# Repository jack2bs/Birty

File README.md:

# Birty the Robot

Birty is a recursive backronym for Birty Is a Robot, Thank You.

As part of my getting acquainted with robotics so as to continue in a leadership capacity in the Princeton Robotics Club, I set out to build a classic and simple, but well designed and well programmed robot which could drive in straight lines, turn accurate angles, avoid obstacles in it's path, and do it all autonomously. While these goals may not sound particularly ambitious or impressive, they are the baseline and the scaffolding for what a robot needs to be able to do.

I am proud of Birty. Birty is my most polished large project to date. The part-selection was, with one exception, well thought out. The electronics are well designed. The 3d structure of the Robot was well planned. The code is well written; it's fast, self-documenting (and documented with comments), and highly functional.

My success building Birty came on the back of the shortcomings of past projects, some of which never lived up to their potential simply due to my mistakes and inexperience. I learned from my mistakes, and I improved. I organized the project better. I worked with each sensor and electrical component before I used them to make sure they functioned as I expected them to. I tested each bit of code before moving onto another function. I took the time to do things right, and in the end it was the fastest I've ever completed a project. 

# Parts and justifications

+ Microcontroller
	+ 1 x [ATMEGA32u4](https://www.digikey.com/en/products/detail/microchip-technology/ATMEGA32U4-AUR/2238241)
	+ The Atmega32u4 is more than powerful enough for the tasks laid out, and since I had experience with it and had some in my supplies (every MCU was out of stock at the time), this was a no-brainer. An I2C bus (using the TWI peripheral) for sensor communications, USART for debugging over bluetooth, GPIO for driving motors, pin change interrupts for reading encoders, and more than enough timers for task scheduling.
+ Distance Sensors
	+ 8 x [Adafruit VL6180x](https://www.adafruit.com/product/3316)
	+ The VL6180x from STM was a good choice because it has great accuracy at low distance ranges which is extremely important for obstacle detection and avoidance for a robot of Birty's size. I chose the 6180x over other sensors in the lineup since it is the only one with a register map available, allowing me to bypass STM's poorly regarded API and simply build an I2C communication layer myself. I chose the Adafruit breakouts so that I wouldn't have to make them myself, and so that I had logic level shifting from 5v to 3.3v on both the interrupt and xshut signal lines.
+ Gyroscope
	+ 1 x [MinImu-9 v5](https://www.pololu.com/product/2738)
	+ This was perhaps the one mistake I made in part selection. The MiniImu-9 v5 from Polulu is a good IMU, but it doesn't have onboard fusion calculation and the speed of the Atmega32u4 makes a complex fusion calculation a challenge. In the future I would lean more towards something like a BNO055 from Bosch, which has on board fusion calculations and outputs roll pitch and yaw, as opposed to x, y, and z for a gyroscope, accelerometer, and magnetometer seperately.
+ Motors
	+ 2 x [Regular DC motors](https://www.adafruit.com/product/4639)
	+ 2 x [Stepper Motors](https://www.adafruit.com/product/4411)
	+ I have both stepper and DC motors and I am able to interchange them as I see fit. The choices here weren't too important but I wanted them as small as I could find, and so that is what I got. 
+ Motor mounts
	+ 1 x [DC Motor Mount](https://www.pololu.com/product/989)
	+ 2 x [Stepper Mount](https://www.pololu.com/product/3435)
+ DC Motor Driver (H Bridge)
	+ 4 x [H Bridges](https://www.adafruit.com/product/4489)
	+ I tested these H bridges on a breadboard before using them on Birty and they proved to be simple and effective.
+ Wheels
	+ 1 x (2 wheels) [Wheel pair](https://www.pololu.com/product/1424)
	+ I wanted somewhat large wheels to attempt to improve Birty's ability to handle semi-rough terrain (carpet).
+ Universal Mounting Hubs
	+ 1 x (2 hubs) [Mounting hub pair](https://www.pololu.com/product/1997)
+ Ball Casters
	+ 2 x [Ball casters](https://www.pololu.com/product/955)
	+ These were so that Birty wouldn't tilt forwards or backwards.
+ Spacers
	+ 1 x [2mm spacers](https://www.pololu.com/product/1980)
	+ 1 x [4mm spacers](https://www.pololu.com/product/1981)
	+ To space the ball casters to the right height.
+ Battery
	+ 1 x [CHAMP Portable Charger](https://www.gonimble.com/products/champ-portable-charger)
	+ I chose this battery pack because it was the smallest I could find and because I am a sucker for sustainability.
+ Battery Mounting
	+ 3 x [Battery Mounts](https://www.pololu.com/product/2677)
	+ I'll explain the battery mounting strategy further when I get to mechanical design.
+ Wire to Board conns
	+ 2 x [6 Pos Wire to Board](https://www.digikey.com/en/products/detail/on-shore-technology-inc/OSTVN06A150/1588866) and 1 x [2 Pos Wire to Board](https://www.digikey.com/en/products/detail/on-shore-technology-inc/OSTVN02A150/1588862)
+ Shift registers
	+  1 x [Shift Register](https://www.digikey.com/en/products/detail/texas-instruments/SN74HCS264DR/13562988)
	+ I'll get into the purpose of the shift register when I discuss the electronics.
+ Assorted SMD Resistors and Capacitors
	+ 3 x 5k R
	+ 2 x 10k R
	+ 1 x 100 R
	+ 2 x 22 R
	+ 6 x 0.1uF C
	+ 1 x 1uF C
	+ 2 x 22pF C
	+ Pushbuttons
	+ 16Mhz Crystal
	+ USB Receptacle
+ Header Pins
	+ 9 x [6 Pos Female Header pins](https://www.digikey.com/en/products/detail/sullins-connector-solutions/PPPC061LFBN-RC/810178)
	+ 1 x [5 Pos Female Header Pins](https://www.digikey.com/en/products/detail/sullins-connector-solutions/PPPC051LFBN-RC/810177)

# Electrical design
After choosing parts I set out to design the schematic and circuit boards. This process was relatively straight forward, except I had to find a way to use as few GPIO pins as possible. The first measure I took was introducing a shift register to access the xshut pins on the 8 VL6180x sensors. I needed to be able to shutdown the sensors one at a time so that I could change their I2C addresses away from their default of 0x29, and so a shift register allowed me to start them all shutdown, and then restart them and set their addresses one at a time. Next, I realized that each of the interrupt pins on the VL6180x sensors could be set as open drain, and thus I could attach them all to one GPIO pin and poll them to see which one triggered an interrupt. These two tricks saved me 6 and 7 GPIO pins each, such that by the end I had 4 extra GPIO pins not being used. The final schematic looked like this:

I took this schematic and used it to produce a circuit board. I wanted every component on the top layer, which was not too difficult considering there was no real size constraint, and I wanted as large of a ground layer on the bottom layer of the board as possible, so I did the vast majority of my routing on the top layer as well. After a few hours of routing I had the following board.

# Mechanical Design
I knew that for a project that would exist in 3d space unlike any project I had done before, I would want to produce a 3d model of Birty so that I knew everything would fit together. It was during this process, I decided, that I would decide on how to mount the motors and battery pack to the robot. The motor mounts were as simple as adding mounting holes, but I knew the battery pack (which had no built in mounting method, seeing as it is just a portable phone charger) would be more difficult. After a significant amount of brainstorming, I decided upon a friction mount system based on stepper motor mounts which had a stiff hinge that allowed them to bend somewhere between -1 and 1 degree away from vertical. This allowed the battery pack to sit in between the mounts, as can be seen in the final picture of Birty at the very bottom of this README.

This was my first experience using Autocad Inventor, but I picked it up relatively quickly and the final product was the following 3d render.

# Programming
As could be expected for a project like this, writing the firmware took the most time. I started with a USART driver since I could use that for debugging, and then moved to an I2C driver so I could communicate with the sensors. Both the USART driver and I2C driver became bases for libraries I have since written. Next I moved onto code for receiving data from each of the sensors and then for communicating with the motors. Next I added some basic PID code for making sure the robot drove straight, and via testing determined that the Integral and Derivative components were not needed in Birty's case (the proportional control was enough). Finally I made sure that Birty could detect and avoid obstacles, or if near by a wall could drive straight and parallel to the wall.

# What went wrong and how did I fix it
Despite the relative success of building Birty, there were some hiccups-two short circuit incidents. The first short circuit occurred due to a lack of insulation between one of the motors and some of the H bridge's through hole pins. This ended up heating up the PCB to the point of destroying a small section of one of the encoder traces. I was fortunate that around a tenth of a millimeter of trace was exposed on either side, and so with a small piece of copper wire and some creative soldering I was able to bridge the damaged trace and cover it with electrical tape such that it has had no issues since. 

The second short circuit occurred when I plugged in the IMU wrong. Fortunately, only the IMU was damaged, and since I had ordered a spare, I was able to slot it in and continue as if nothing had happened. In addition, the IMU ended up being my least used sensor since I didn't want to give up clock cycles to a complicated fusion algorithm throughout my testing of Birty.

# Finally
Here are some pictures of Birty in my dorm room this year. Building Birty proved to me that when engineering is done right, it can be smooth and highly effective, which only reinforced just how beautiful this stuff can really be!

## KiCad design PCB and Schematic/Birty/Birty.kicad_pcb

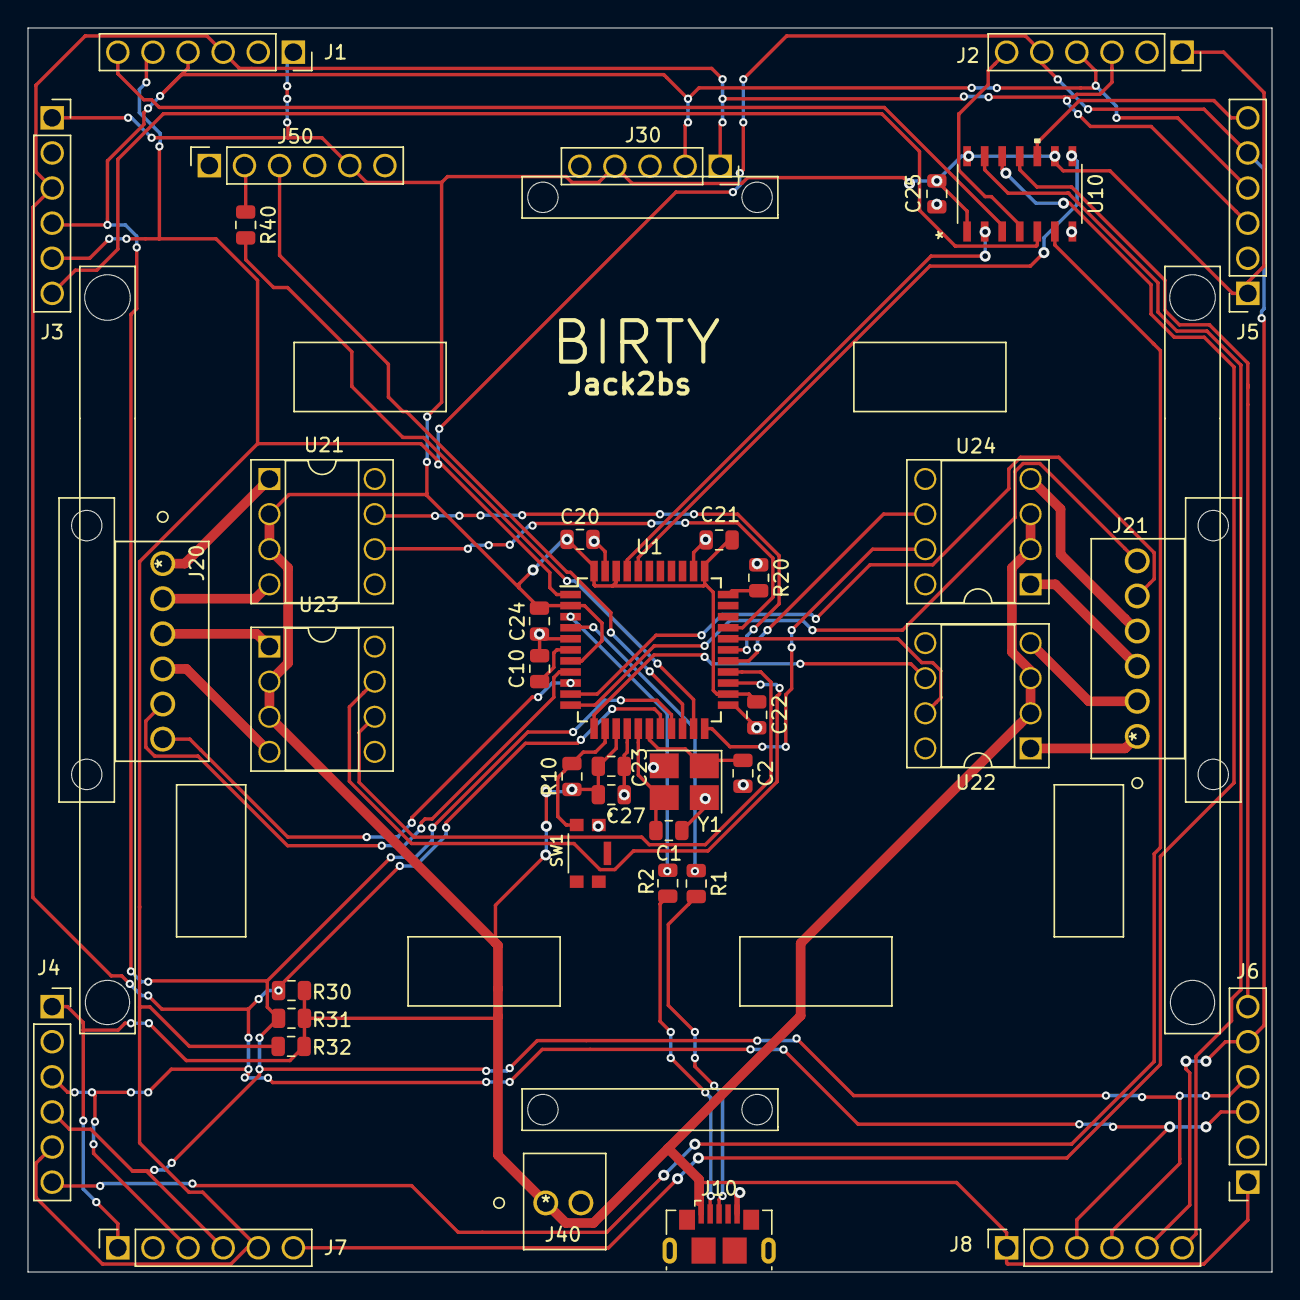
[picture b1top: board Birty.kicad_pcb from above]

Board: 2 copper layers, 90.0 x 90.0 mm, 40 parts (0 on the bottom side), 47 nets.

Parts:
C1, C2: 22pF; C_0805_2012Metric
C10: 1uF; C_0805_2012Metric
C20, C21, C22, C23, C24, C25: 0.1uF; C_0805_2012Metric
C27: 10uF; C_0805_2012Metric
J1, J2, J3, J4, J5, J6, J7, J8: VL6180AdaFruit; VL6810AdaFruit
J10: USB_mini_micro_B; USB_Micro-B_GCT_USB3076-30-A
J20, J21: OSTVN06A150
J30: MinIMU-9_v5_Conn; MiniIMU-9-v5
J40: OSTVN02A150
J50: HC05Header
R1, R2: 22r; R_0805_2012Metric
R10, R20: 10k; R_0805_2012Metric
R30, R31: 4k7; R_0805_2012Metric
R32: 5k; R_0805_2012Metric
R40: 100r; R_0805_2012Metric
SW1: SW_PUSH; SW_KMR421GULCLFS
U1: ATmega32U4-AU; TQFP-44_10x10mm_P0.8mm
U10: SN74HCS264DR
U21, U22, U23, U24: L9110_HBridge; Adafruit_L9110_HBridge
Y1: 16Mhz; Crystal_SMD_3225-4Pin_3.2x2.5mm_HandSoldering

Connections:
+5V: C20.1, C21.1, C22.1, C23.1, C24.1, C25.1, C27.1, J1.1, J2.1, J3.1, J4.1, J5.1, J6.1, J7.1, J8.1, J10.1, J30.4, J40.1, J50.5, R10.1, R30.2, R31.1, R32.1, U1.2, U1.7, U1.14, U1.24, U1.34, U1.42, U1.44, U10.1, U10.9, U10.14, U21.2, U21.3, U22.2, U22.3, U23.2, U23.3, U24.2, U24.3
D+: J10.3, R1.2
D-: J10.2, R2.2
ENC11: J20.5, U1.8
ENC12: J20.6, U1.9
ENC21: J21.5, U1.10
ENC22: J21.6, U1.11
GND: C1.1, C2.2, C10.2, C20.2, C21.2, C22.2, C23.2, C24.2, C25.2, C27.2, J1.2, J2.2, J3.2, J4.2, J5.2, J6.2, J7.2, J8.2, J10.5, J10.6, J30.3, J40.2, J50.4, R20.1, SW1.1, U1.5, U1.15, U1.23, U1.35, U1.43, U10.7, U21.5, U21.8, U22.5, U22.8, U23.5, U23.8, U24.5, U24.8, Y1.2, Y1.4
M11: J20.1, U21.1
M12: J20.2, U21.4
M13: J20.3, U23.1
M14: J20.4, U23.4
M21: J21.1, U22.1
M22: J21.2, U22.4
M23: J21.3, U24.1
M24: J21.4, U24.4
unnamed: C1.2, U1.16, Y1.3
unnamed: C2.1, U1.17, Y1.1
unnamed: C10.1, U1.6
unnamed: J50.2, R40.1
unnamed: R1.1, U1.4
unnamed: R2.1, U1.3
unnamed: R10.2, SW1.2, U1.13
unnamed: R20.2, U1.33
PB4: U1.28, U21.7
PB5: U1.29, U22.7
PB6: U1.30, U21.6
PB7: U1.12, U22.6
PD4: U1.25, U23.7
PD5: U1.22, U24.7
PD6: U1.26, U23.6
PD7: U1.27, U24.6
PE6: J1.5, J2.5, J3.5, J4.5, J5.5, J6.5, J7.5, J8.5, R32.2, U1.1
PF0: U1.41, U10.2
PF1: U1.40, U10.8
RXA: J50.3, U1.20
SCL: J1.3, J2.3, J3.3, J4.3, J5.3, J6.3, J7.3, J8.3, J30.1, R30.1, U1.18
SDA: J1.4, J2.4, J3.4, J4.4, J5.4, J6.4, J7.4, J8.4, J30.2, R31.2, U1.19
TXA: R40.2, U1.21
XS1: J1.6, U10.3
XS2: J2.6, U10.4
XS3: J3.6, U10.5
XS4: J4.6, U10.6
XS5: J5.6, U10.10
XS6: J6.6, U10.11
XS7: J7.6, U10.12
XS8: J8.6, U10.13

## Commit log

2022-07-03 Updated Wall in front threshold
2022-09-16 Added inline qualifier to getDistSensorDist()
2022-09-16 Remove inline just in case
2022-10-16 renamed project and solution
2022-10-16 Added some photos

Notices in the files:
parts and their libraries:
Copyright 2021 Accelerated Designs. All rights reserved.
